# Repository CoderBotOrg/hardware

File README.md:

# CoderBot Hardware designs

This repo contains the designs (schematics, boards) for the CoderBot "Hat" for Raspberry Pi (B+ and beyond).

The Hat has the following features:

- 2 DC motor control, with encoder
- 1 push button
- 4 distance sensors (hc-sr04)
- 1 MPU (Accelerometer, Gyroscope, Magnetometer, Temperature sensor)
- 1 microcontroller with 2 AD + 16 digital GPIO

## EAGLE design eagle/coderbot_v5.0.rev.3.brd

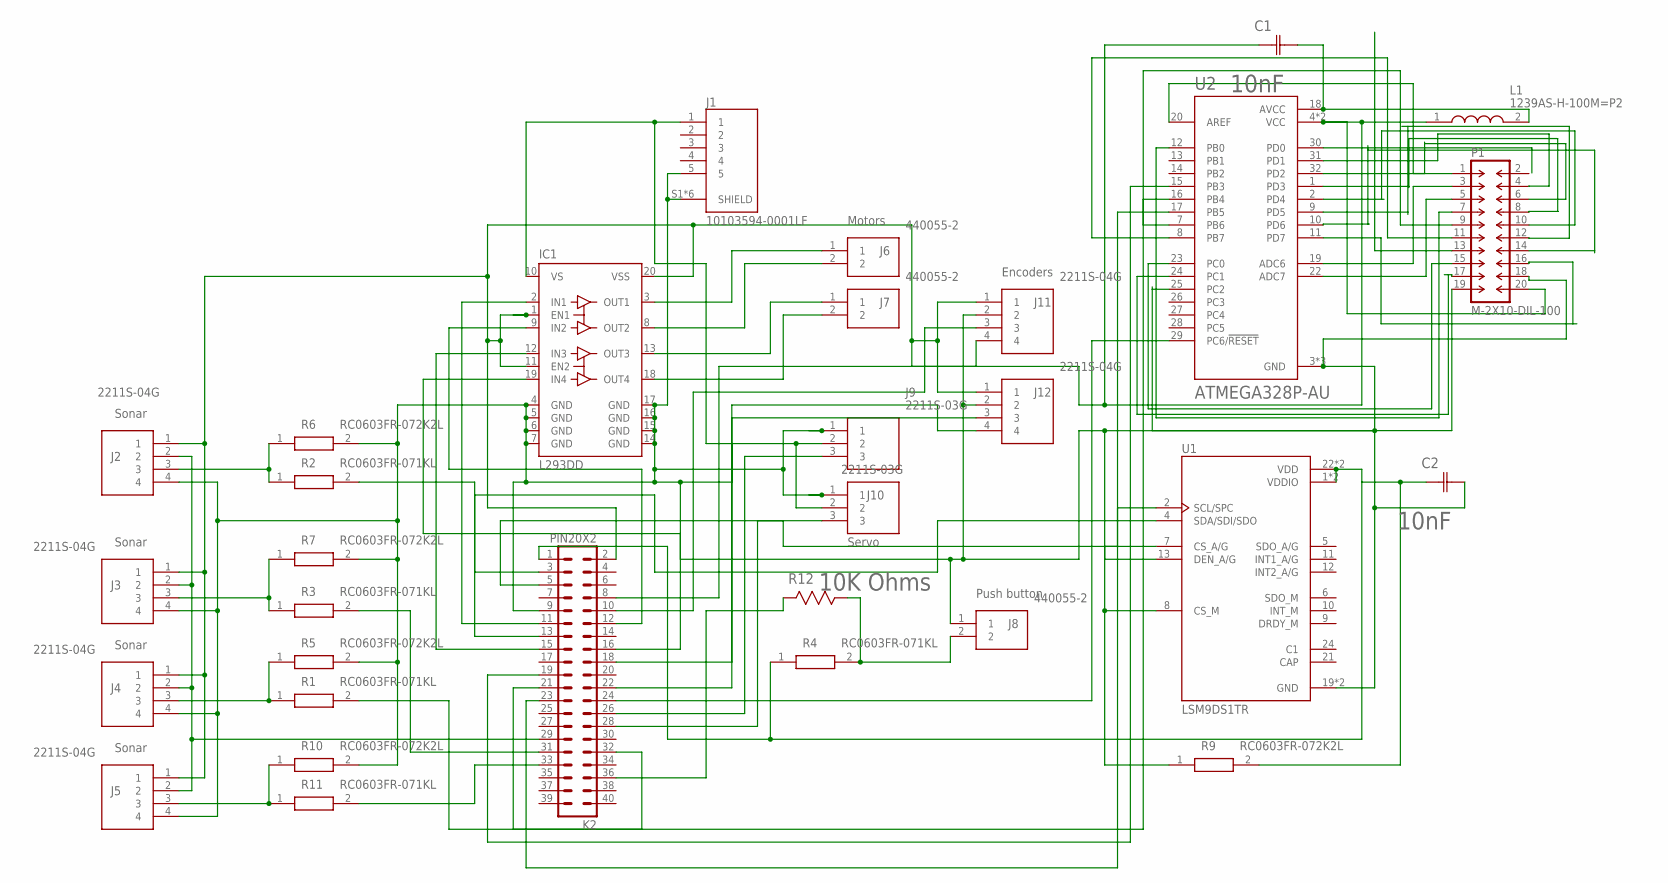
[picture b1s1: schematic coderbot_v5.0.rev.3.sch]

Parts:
C1, C2: 10nF; CAPC1005X55N
IC1: L293DD; SO20
J1: 10103594-0001LF; FCI_10103594-0001LF
J2, J3, J4, J5, J11, J12: 2211S-04G; HDRV4W90P0X254_1X4_1016X254X87
J6, J7, J8: 440055-2; SHDR2W70P0X200_1X2_600X770X525
J9, J10: 2211S-03G; HDRV3W90P0X254_1X3_762X254X874
K2: PIN20X2; PIN_20X2
L1: 1239AS-H-100M=P2; INDC2520X120N
P1: M-2X10-DIL-100; DIL-100-2X10
R1, R2, R3, R4, R11: RC0603FR-071KL; RESC1608X55N
R5, R6, R7, R9, R10: RC0603FR-072K2L; RESC1608X55N
R12: 10K Ohms; RESC1608X60N
U1: LSM9DS1TR; PQFN43P300X350X102-24N
U2: ATMEGA328P-AU; QFP80P900X900X120-32N

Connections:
GND: C2.2 (C2), IC1.4 (GND), IC1.5 (GND), IC1.6 (GND), IC1.7 (GND), IC1.14 (GND), IC1.15 (GND), IC1.16 (GND), IC1.17 (GND), J1.5, J1.S1 (SHIELD), J1.S2 (SHIELD), J1.S3 (SHIELD), J1.S4 (SHIELD), J1.S5 (SHIELD), J1.S6 (SHIELD), J2.4, J3.4, J4.4, J5.4, J8.1, J9.1, J10.1, J11.2, J12.2, K2.9, P1.18, R5.2, R6.2, R7.2, R10.2, U1.13 (DEN_A/G), U1.19 (GND), U1.20 (GND), U2.3 (GND), U2.5 (GND), U2.21 (GND)
unnamed: IC1.3 (OUT1), J6.1
unnamed: IC1.8 (OUT2), J6.2
unnamed: IC1.13 (OUT3), J7.1
unnamed: IC1.18 (OUT4), J7.2
unnamed: K2.13, R2.2
unnamed: J2.2, J3.2, J4.2, J5.2, K2.29
unnamed: J2.3, R2.1, R6.1
unnamed: C1.1 (C1), IC1.1 (EN1), IC1.11 (EN2), IC1.20 (VSS), J2.1, J3.1, J4.1, J5.1, J11.1, J12.1, K2.2, L1.1, P1.20, U2.4 (VCC), U2.6 (VCC)
unnamed: J3.3, R3.1, R7.1
unnamed: J8.2, R4.2, R12.1 (R1)
unnamed: J11.4, K2.8
unnamed: IC1.10 (VS), J1.1, J9.2, J10.2
unnamed: J4.3, R1.1, R5.1
unnamed: J12.4, K2.22
unnamed: J12.3, K2.18
unnamed: K2.3, U1.4 (SDA/SDI/SDO)
unnamed: K2.5, U1.2 (SCL/SPC)
unnamed: IC1.2 (IN1), K2.11
unnamed: IC1.9 (IN2), K2.12
unnamed: IC1.12 (IN3), K2.15
unnamed: IC1.19 (IN4), K2.16
unnamed: K2.19, U2.15 (PB3)
unnamed: K2.31, R3.2
unnamed: K2.32, R1.2
unnamed: J5.3, R10.1, R11.1
unnamed: J11.3, K2.10
unnamed: K2.21, U2.16 (PB4)
unnamed: K2.23, U2.17 (PB5)
unnamed: K2.24, U2.29 (PC6/!RESET)
unnamed: C2.1 (C1), K2.1, R4.1, R9.2, U1.1 (VDDIO), U1.3 (VDDIO), U1.22 (VDD), U1.23 (VDD)
unnamed: R9.1, U1.7 (CS_A/G), U1.8 (CS_M)
unnamed: C1.2 (C2), L1.2, U2.18 (AVCC)
unnamed: J9.3, K2.26
unnamed: K2.33, R11.2
unnamed: J10.3, K2.28
unnamed: P1.1, U2.20 (AREF)
unnamed: P1.3, U2.19 (ADC6)
unnamed: P1.5, U2.22 (ADC7)
unnamed: P1.7, U2.12 (PB0)
unnamed: P1.9, U2.7 (PB6)
unnamed: P1.11, U2.8 (PB7)
unnamed: P1.15, U2.23 (PC0)
unnamed: P1.17, U2.24 (PC1)
unnamed: P1.19, U2.25 (PC2)
unnamed: P1.4, U2.31 (PD1)
unnamed: P1.6, U2.32 (PD2)
unnamed: P1.8, U2.1 (PD3)
unnamed: P1.10, U2.2 (PD4)
unnamed: P1.12, U2.9 (PD5)
unnamed: P1.14, U2.10 (PD6)
unnamed: P1.16, U2.11 (PD7)
unnamed: K2.36, R12.2 (R2)

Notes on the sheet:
Motors
Encoders
Servo
Push button
Sonar

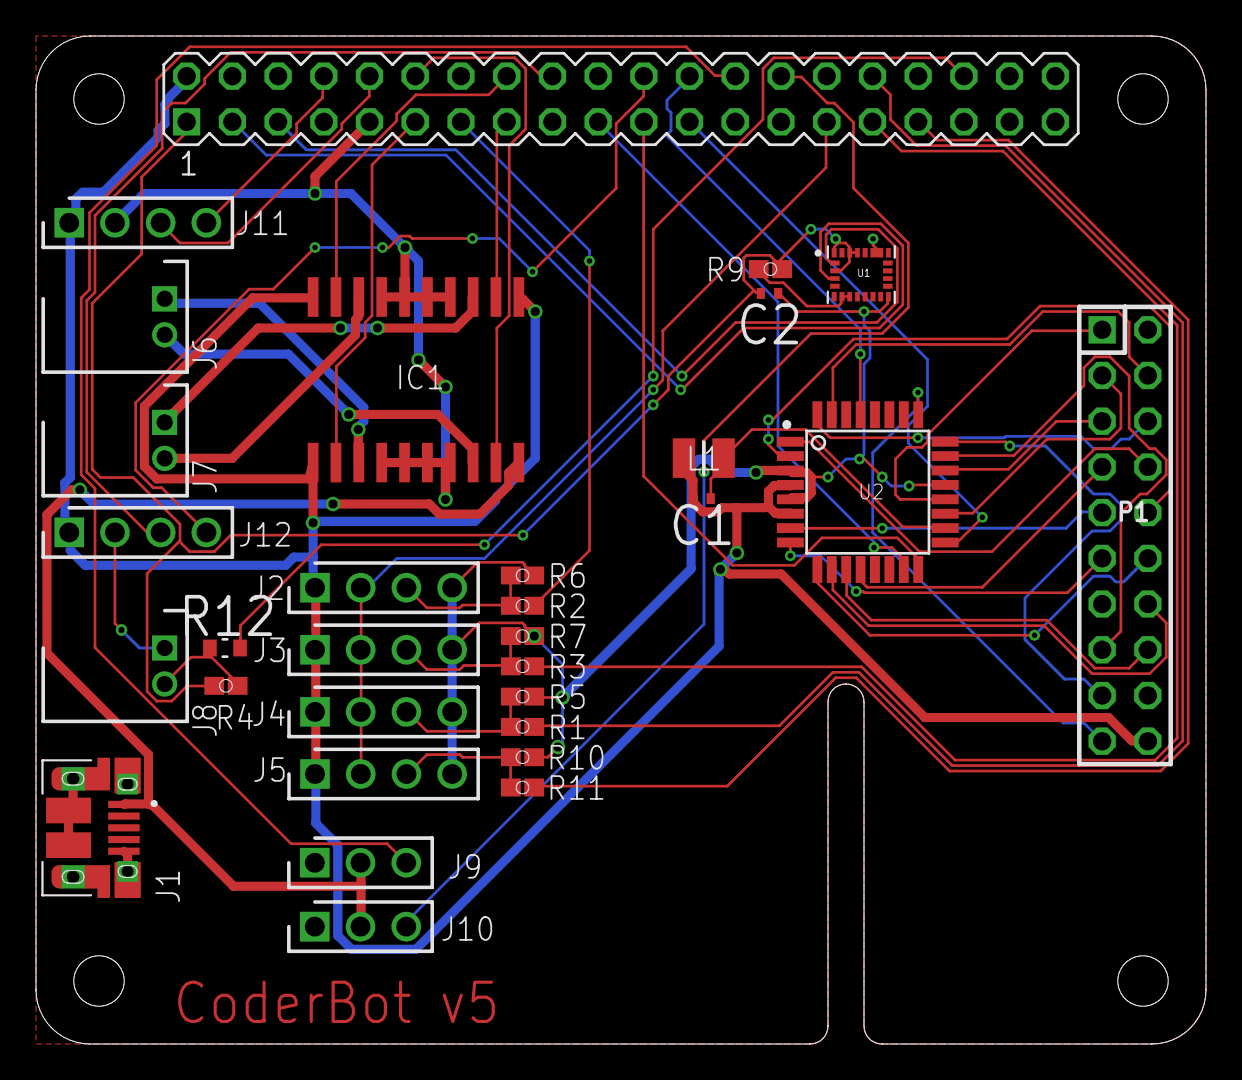
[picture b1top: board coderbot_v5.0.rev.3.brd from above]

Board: 2 copper layers, 65.0 x 56.0 mm, 31 parts (0 on the bottom side), 53 nets.

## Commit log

2020-01-02 first

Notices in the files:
parts and their libraries:
con-headers-jp: Copyright (C) 2008, Bob Starr
